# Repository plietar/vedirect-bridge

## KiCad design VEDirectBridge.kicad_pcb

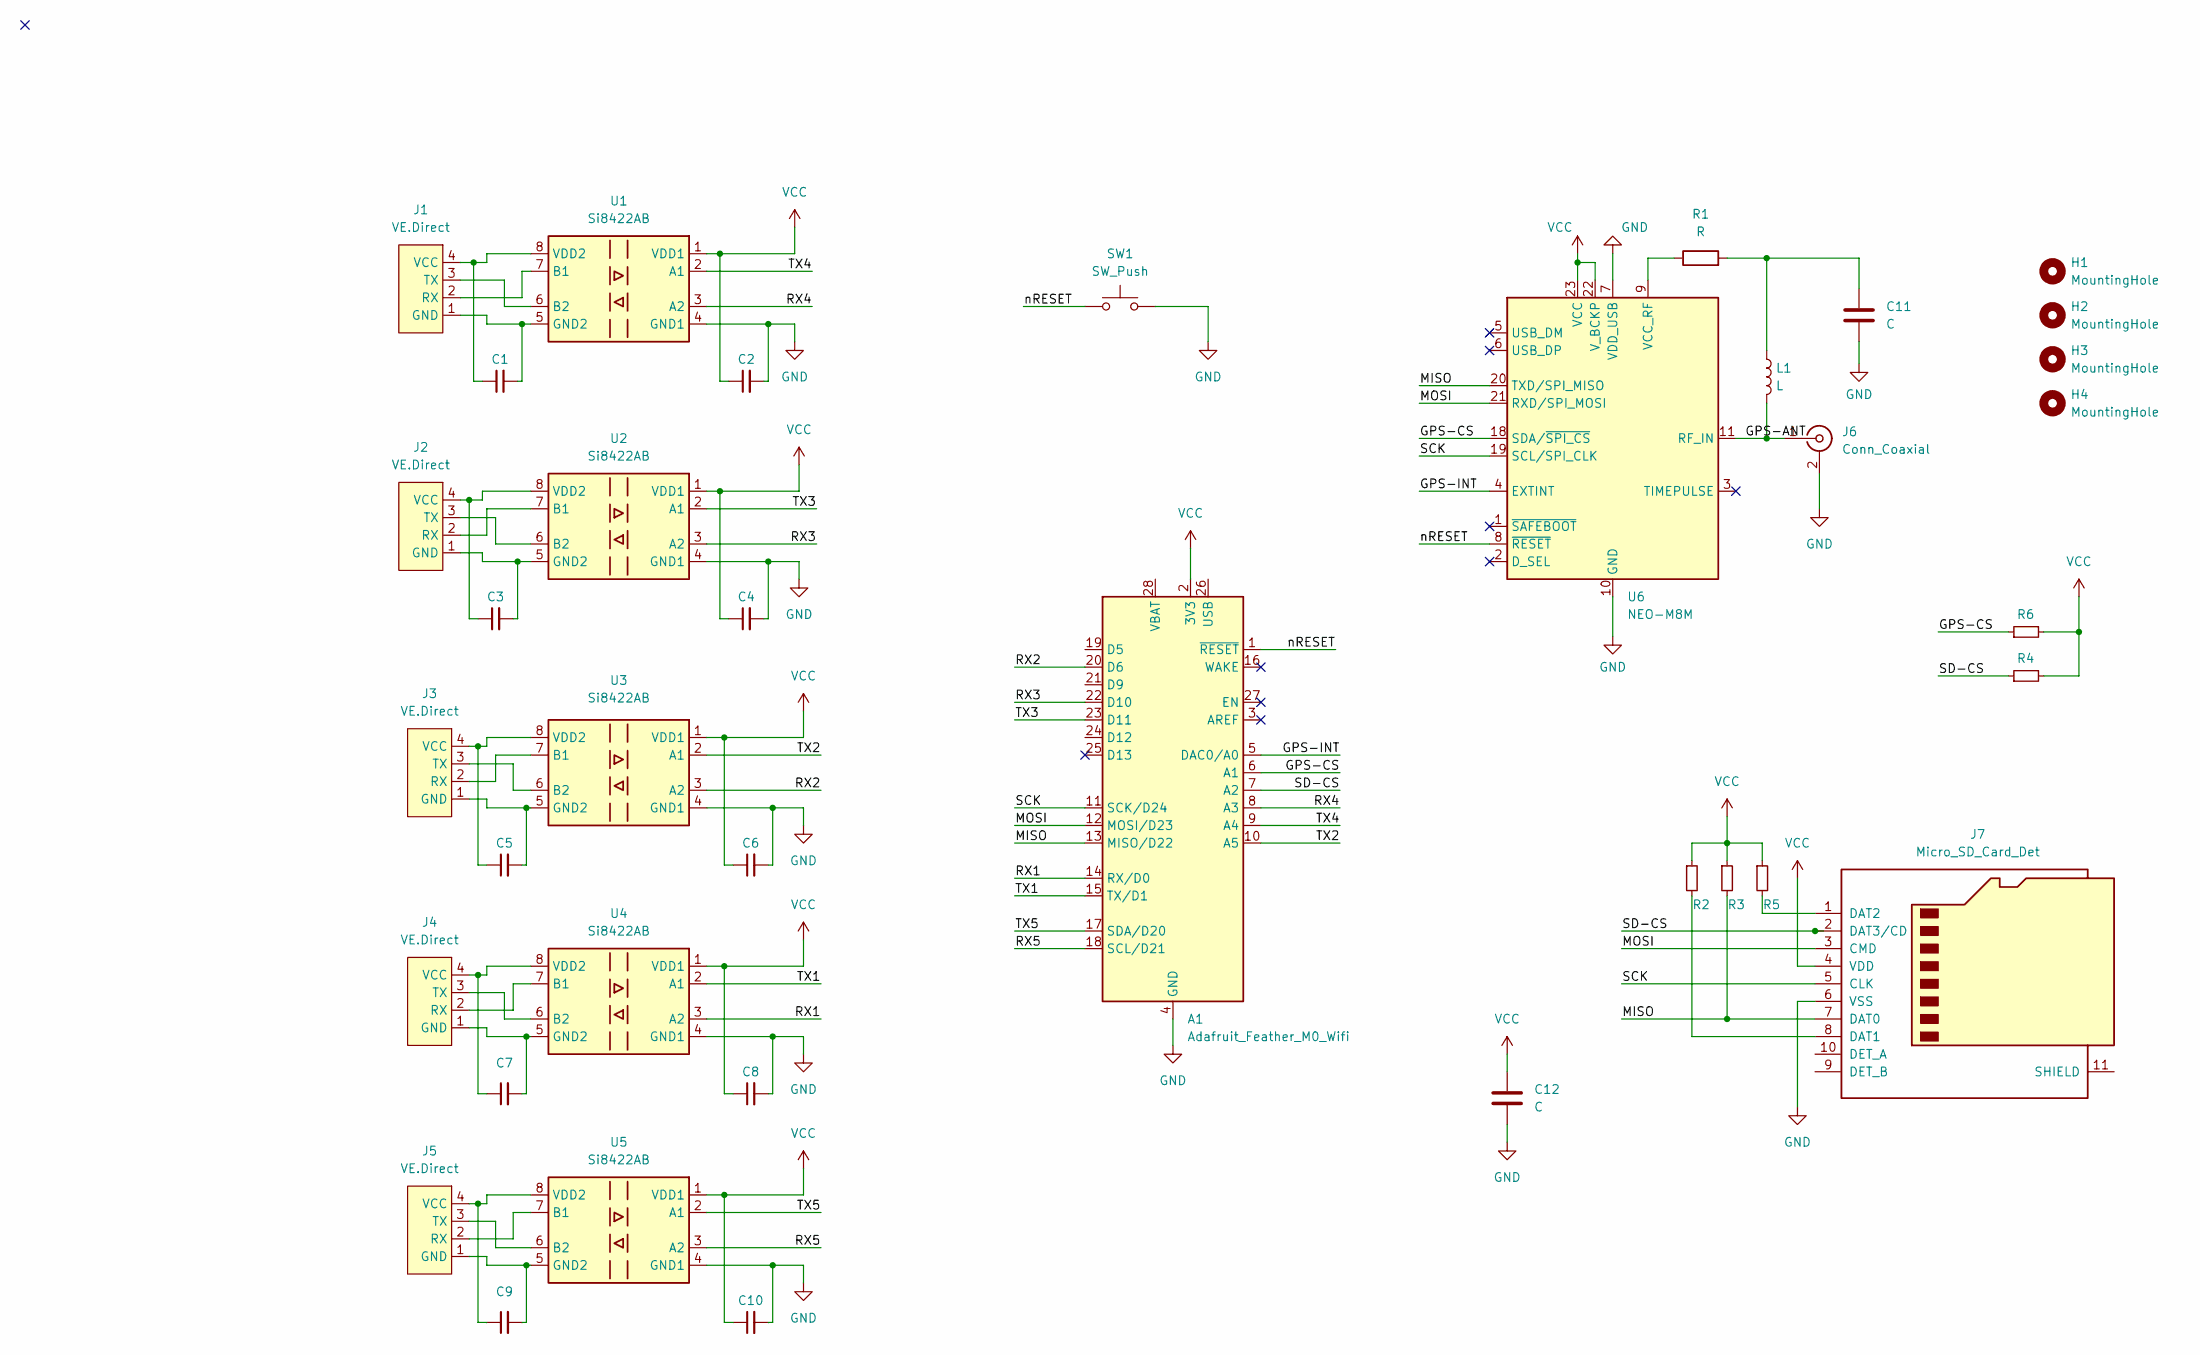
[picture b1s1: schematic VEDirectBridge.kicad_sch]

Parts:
A1: Adafruit_Feather_M0_Wifi
C1, C2, C3, C4, C5, C6, C7, C8, C9, C10: C_Small; C_0603_1608Metric_Pad1.08x0.95mm_HandSolder
C11, C12: C; C_0603_1608Metric_Pad1.08x0.95mm_HandSolder
H1, H2, H3, H4: MountingHole; MountingHole_2.7mm_M2.5
J1, J2, J3, J4, J5: VE.Direct; JST_PH_S4B-PH-SM4-TB_1x04-1MP_P2.00mm_Horizontal
J6: Conn_Coaxial; SMA_Molex_73251-2120_EdgeMount_Horizontal
J7: Micro_SD_Card_Det; microSD_HC_Hirose_DM3AT-SF-PEJM5
L1: L; L_0603_1608Metric_Pad1.05x0.95mm_HandSolder
R1: R; R_0603_1608Metric_Pad0.98x0.95mm_HandSolder
R2, R3, R4, R5, R6: R_Small; R_0603_1608Metric_Pad0.98x0.95mm_HandSolder
SW1: SW_Push; SW_Push_1P1T_NO_6x6mm_H9.5mm
U1, U2, U3, U4, U5: Si8422AB; SOIC-8_3.9x4.9mm_P1.27mm
U6: NEO-M8M; ublox_NEO

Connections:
/GPS-ANT: J6.1 (In), L1.2, U6.11 (RF_IN)
/GPS-CS: A1.6 (A1), R6.1, U6.18 (SDA/~SPI_CS)
/GPS-INT: A1.5 (DAC0/A0), U6.4 (EXTINT)
/MISO: A1.13 (MISO/D22), J7.7 (DAT0), R3.2, U6.20 (TXD/SPI_MISO)
/MOSI: A1.12 (MOSI/D23), J7.3 (CMD), U6.21 (RXD/SPI_MOSI)
/RX1: A1.14 (RX/D0), U4.3 (A2)
/RX2: A1.20 (D6), U3.3 (A2)
/RX3: A1.22 (D10), U2.3 (A2)
/RX4: A1.8 (A3), U1.3 (A2)
/RX5: A1.18 (SCL/D21), U5.3 (A2)
/SCK: A1.11 (SCK/D24), J7.5 (CLK), U6.19 (SCL/SPI_CLK)
/SD-CS: A1.7 (A2), J7.2 (DAT3/CD), R4.1
/TX1: A1.15 (TX/D1), U4.2 (A1)
/TX2: A1.10 (A5), U3.2 (A1)
/TX3: A1.23 (D11), U2.2 (A1)
/TX4: A1.9 (A4), U1.2 (A1)
/TX5: A1.17 (SDA/D20), U5.2 (A1)
/nRESET: A1.1 (~RESET), SW1.1, U6.8 (~RESET)
GND: A1.4 (GND), C2.2, C4.2, C6.2, C8.2, C10.2, C11.2, C12.2, J6.2 (Ext), J7.6 (VSS), SW1.2, U1.4 (GND1), U2.4 (GND1), U3.4 (GND1), U4.4 (GND1), U5.4 (GND1), U6.7 (VDD_USB), U6.10 (GND), U6.12 (GND), U6.13 (GND), U6.24 (GND)
unnamed: C1.1, J1.4 (VCC), U1.8 (VDD2)
unnamed: C1.2, J1.1 (GND), U1.5 (GND2)
unnamed: C3.1, J2.4 (VCC), U2.8 (VDD2)
unnamed: C3.2, J2.1 (GND), U2.5 (GND2)
unnamed: C5.1, J3.4 (VCC), U3.8 (VDD2)
unnamed: C5.2, J3.1 (GND), U3.5 (GND2)
unnamed: C7.1, J4.4 (VCC), U4.8 (VDD2)
unnamed: C7.2, J4.1 (GND), U4.5 (GND2)
unnamed: C9.1, J5.4 (VCC), U5.8 (VDD2)
unnamed: C9.2, J5.1 (GND), U5.5 (GND2)
unnamed: C11.1, L1.1, R1.2
unnamed: J1.2 (RX), U1.7 (B1)
unnamed: J1.3 (TX), U1.6 (B2)
unnamed: J2.2 (RX), U2.7 (B1)
unnamed: J2.3 (TX), U2.6 (B2)
unnamed: J3.2 (RX), U3.7 (B1)
unnamed: J3.3 (TX), U3.6 (B2)
unnamed: J4.2 (RX), U4.7 (B1)
unnamed: J4.3 (TX), U4.6 (B2)
unnamed: J5.2 (RX), U5.7 (B1)
unnamed: J5.3 (TX), U5.6 (B2)
unnamed: J7.1 (DAT2), R5.2
unnamed: J7.8 (DAT1), R2.2
unnamed: R1.1, U6.9 (VCC_RF)
VCC: A1.2 (3V3), C2.1, C4.1, C6.1, C8.1, C10.1, C12.1, J7.4 (VDD), R2.1, R3.1, R4.2, R5.1, R6.2, U1.1 (VDD1), U2.1 (VDD1), U3.1 (VDD1), U4.1 (VDD1), U5.1 (VDD1), U6.22 (V_BCKP), U6.23 (VCC)

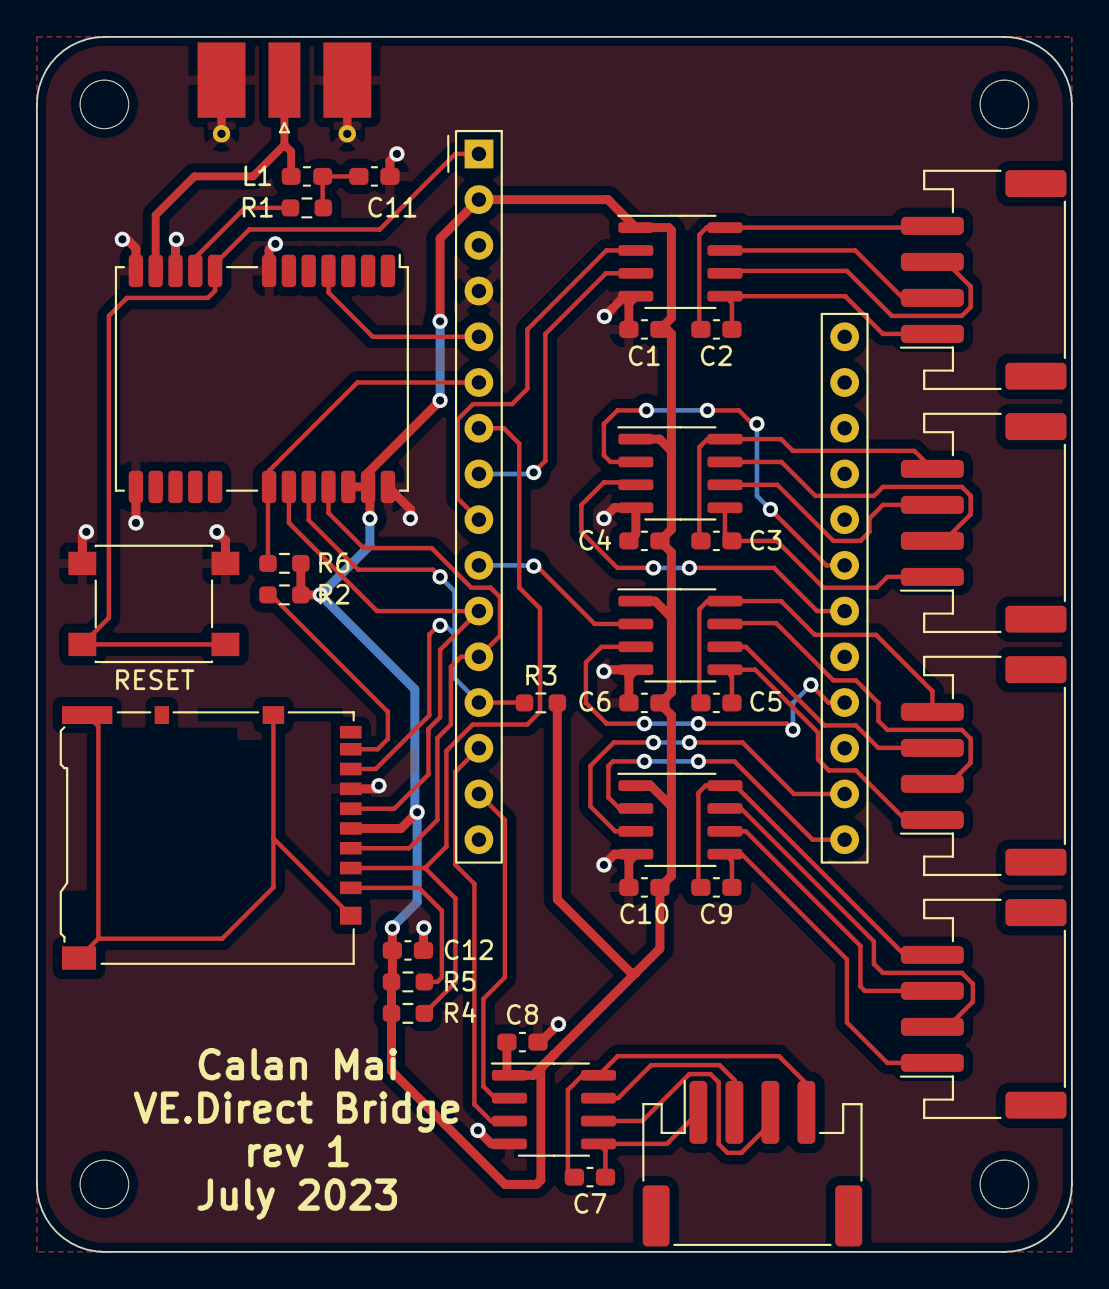
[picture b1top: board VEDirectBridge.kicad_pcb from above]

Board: 2 copper layers, 57.5 x 67.5 mm, 38 parts (0 on the bottom side), 44 nets.

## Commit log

2023-07-03 Initial commit.
2023-07-03 rev1
